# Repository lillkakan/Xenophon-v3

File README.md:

# Xenophon v3 split keyboard

Xenophon is a split keyboard with a design based on the ErgoDox EZ but for less keys for the thumps and another layout for the side keys.

## Features

### Ortholinear design

The keyboard features an ortholinear design based on the ErgoDox EZ.

### 70 buttons

The keyboard features 70 buttons to replicate a standard 60% keyboard as much as possible.
The Default layout is in swedish and has all the letters and numbers.

### TRS jack connection

The PCB is designed with a trs jack nicley placed between the tilted keys.
The two processors sent data through the serial bitbang protocol.

### Smart flashing design

With Usb on both sides it's easy to flash both processors.

### USB-C

The PCB features two usb type c ports with capability to connect via a usb-c to usb-c cable or a standard usb-c to usb-a cable.

### 3D printable chassi

The chassi for the keyboard is 3D printable and is designed to be as small as possible while still protecting the PCB and the electrical components.

## Made with

Quantum Mechanical Keyboard Firmware: [qmk_firmware](https://github.com/qmk/qmk_firmware)

### Made with help from

Keyboard layout editor: [keyboard-layout-editor.com](http://www.keyboard-layout-editor.com/)

Parametric Mechanical Keycap Library: [KeyV2](https://github.com/rsheldiii/KeyV2)

Keyboard Firmware Builder: [kbfirmware.com](https://kbfirmware.com/)

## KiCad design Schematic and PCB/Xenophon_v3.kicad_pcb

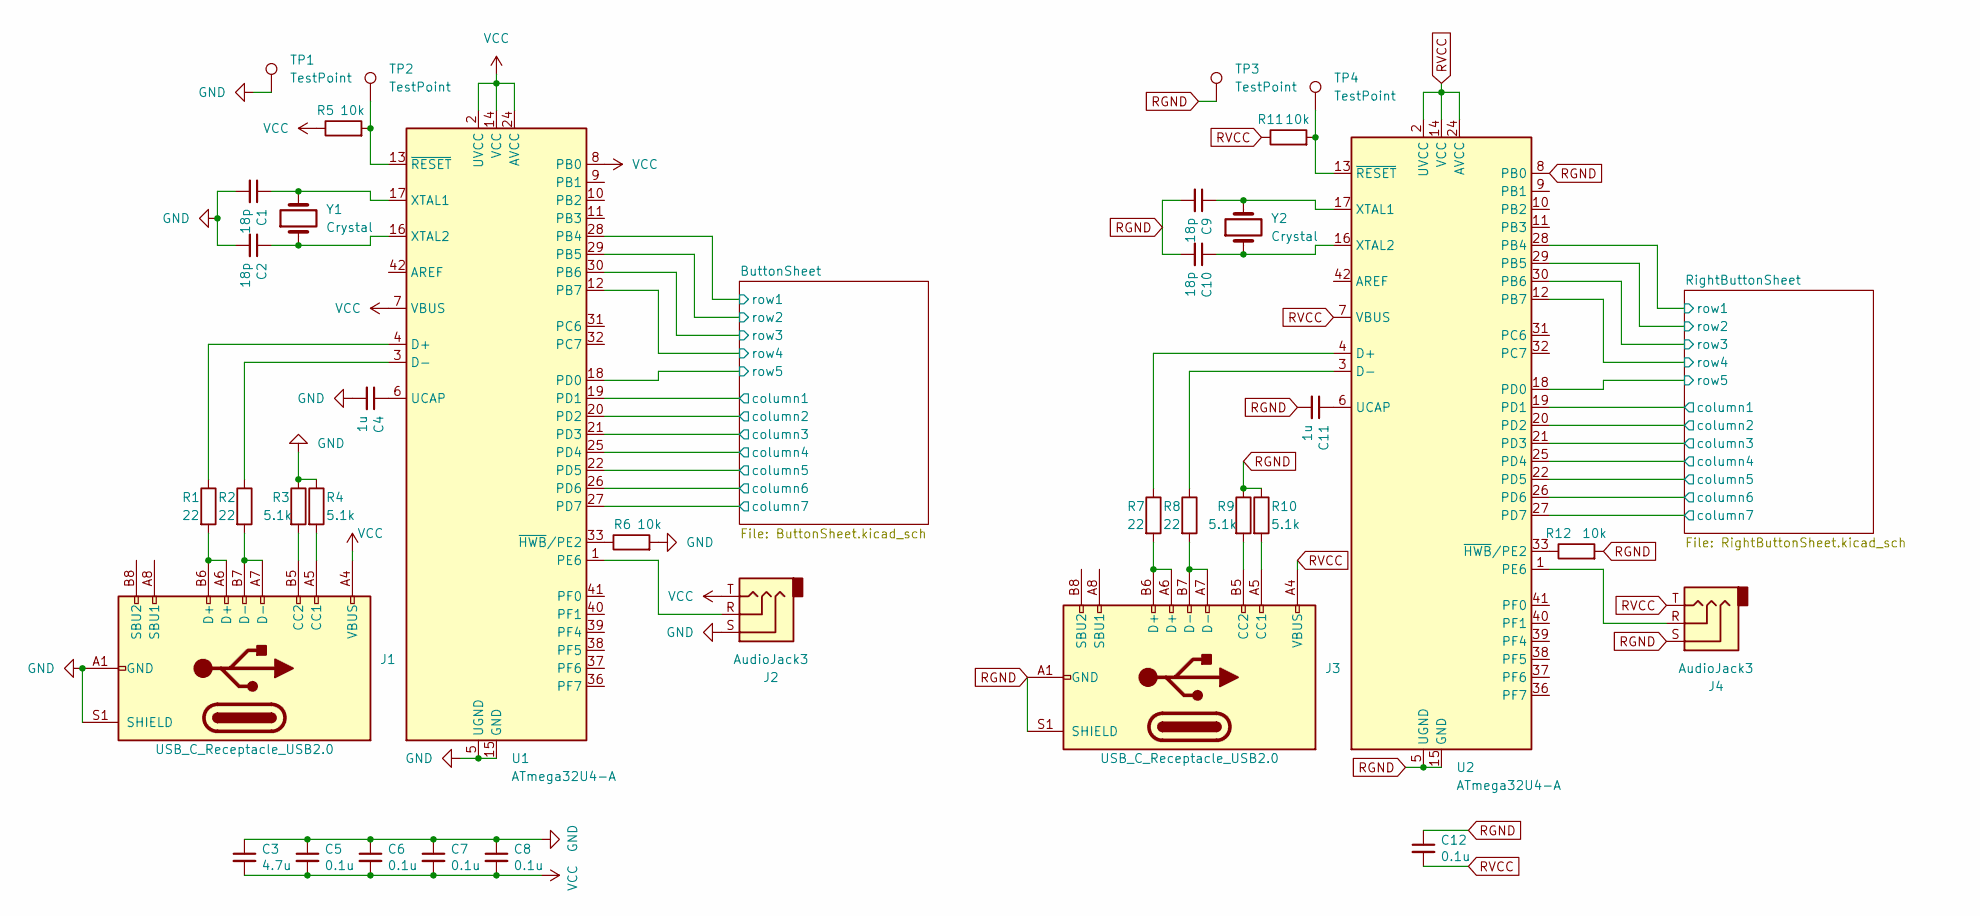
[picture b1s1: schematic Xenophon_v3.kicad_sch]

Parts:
C1, C2, C9, C10: 18p; C_1206_3216Metric
C3: 4.7u; C_1206_3216Metric
C4, C11: 1u; C_1206_3216Metric
C5, C6, C7, C8, C12: 0.1u; C_1206_3216Metric
J1, J3: USB_C_Receptacle_USB2.0; USB_C_Receptacle_HRO_TYPE-C-31-M-12
J2, J4: AudioJack3; Jack_3.5mm_Switronic_ST-005-G_horizontal
R1, R2, R7, R8: 22; R_1206_3216Metric
R3, R4, R9, R10: 5.1k; R_1206_3216Metric
R5, R6, R11, R12: 10k; R_1206_3216Metric
TP1, TP2, TP3, TP4: TestPoint; TestPoint_THTPad_2.0x2.0mm_Drill1.0mm
U1, U2: ATmega32U4-A; TQFP-44_10x10mm_P0.8mm
Y1, Y2: Crystal; Crystal_SMD_2016-4Pin_2.0x1.6mm

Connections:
/ButtonSheet/column1: U1.19 (PD1); also elsewhere on the board
/ButtonSheet/column2: U1.20 (PD2); also elsewhere on the board
/ButtonSheet/column3: U1.21 (PD3); also elsewhere on the board
/ButtonSheet/column4: U1.25 (PD4); also elsewhere on the board
/ButtonSheet/column5: U1.22 (PD5); also elsewhere on the board
/ButtonSheet/column6: U1.26 (PD6); also elsewhere on the board
/ButtonSheet/column7: U1.27 (PD7); also elsewhere on the board
/ButtonSheet/row1: U1.28 (PB4); also elsewhere on the board
/ButtonSheet/row2: U1.29 (PB5); also elsewhere on the board
/ButtonSheet/row3: U1.30 (PB6); also elsewhere on the board
/ButtonSheet/row4: U1.12 (PB7); also elsewhere on the board
/ButtonSheet/row5: U1.18 (PD0); also elsewhere on the board
/RightButtonSheet/column1: U2.19 (PD1); also elsewhere on the board
/RightButtonSheet/column2: U2.20 (PD2); also elsewhere on the board
/RightButtonSheet/column3: U2.21 (PD3); also elsewhere on the board
/RightButtonSheet/column4: U2.25 (PD4); also elsewhere on the board
/RightButtonSheet/column5: U2.22 (PD5); also elsewhere on the board
/RightButtonSheet/column6: U2.26 (PD6); also elsewhere on the board
/RightButtonSheet/column7: U2.27 (PD7); also elsewhere on the board
/RightButtonSheet/row1: U2.28 (PB4); also elsewhere on the board
/RightButtonSheet/row2: U2.29 (PB5); also elsewhere on the board
/RightButtonSheet/row3: U2.30 (PB6); also elsewhere on the board
/RightButtonSheet/row4: U2.12 (PB7); also elsewhere on the board
/RightButtonSheet/row5: U2.18 (PD0); also elsewhere on the board
GND: C1.2, C2.2, C3.1, C4.2, C5.1, C6.1, C7.1, C8.1, J1.A1 (GND), J1.A12 (GND), J1.B1 (GND), J1.B12 (GND), J1.S1 (SHIELD), J2.S, R3.1, R4.1, R6.2, TP1.1, U1.5 (UGND), U1.15 (GND), U1.23 (GND), U1.35 (GND), U1.43 (GND), Y1.3, Y1.4
unnamed: C1.1, U1.17 (XTAL1), Y1.2
unnamed: C2.1, U1.16 (XTAL2), Y1.1
unnamed: C4.1, U1.6 (UCAP)
unnamed: C9.1, U2.17 (XTAL1), Y2.2
unnamed: C10.1, U2.16 (XTAL2), Y2.1
unnamed: C11.1, U2.6 (UCAP)
unnamed: J1.A5 (CC1), R4.2
unnamed: J1.A6 (D+), J1.B6 (D+), R1.2
unnamed: J1.A7 (D-), J1.B7 (D-), R2.2
unnamed: J1.B5 (CC2), R3.2
unnamed: J2.R, U1.1 (PE6)
unnamed: J3.A5 (CC1), R10.2
unnamed: J3.B5 (CC2), R9.2
unnamed: J3.A6 (D+), J3.B6 (D+), R7.2
unnamed: J3.A7 (D-), J3.B7 (D-), R8.2
unnamed: J4.R, U2.1 (PE6)
unnamed: R1.1, U1.4 (D+)
unnamed: R2.1, U1.3 (D-)
unnamed: R5.2, TP2.1, U1.13 (~RESET)
unnamed: R6.1, U1.33 (~HWB/PE2)
unnamed: R7.1, U2.4 (D+)
unnamed: R8.1, U2.3 (D-)
unnamed: R11.2, TP4.1, U2.13 (~RESET)
unnamed: R12.1, U2.33 (~HWB/PE2)
RGND: C9.2, C10.2, C11.2, C12.1, J3.A1 (GND), J3.A12 (GND), J3.B1 (GND), J3.B12 (GND), J3.S1 (SHIELD), J4.S, R9.1, R10.1, R12.2, TP3.1, U2.5 (UGND), U2.8 (PB0), U2.15 (GND), U2.23 (GND), U2.35 (GND), U2.43 (GND), Y2.3, Y2.4
RVCC: C12.2, J3.A4 (VBUS), J3.A9 (VBUS), J3.B4 (VBUS), J3.B9 (VBUS), J4.T, R11.1, U2.2 (UVCC), U2.7 (VBUS), U2.14 (VCC), U2.24 (AVCC), U2.34 (VCC), U2.44 (AVCC)
VCC: C3.2, C5.2, C6.2, C7.2, C8.2, J1.A4 (VBUS), J1.A9 (VBUS), J1.B4 (VBUS), J1.B9 (VBUS), J2.T, R5.1, U1.2 (UVCC), U1.7 (VBUS), U1.8 (PB0), U1.14 (VCC), U1.24 (AVCC), U1.34 (VCC), U1.44 (AVCC)

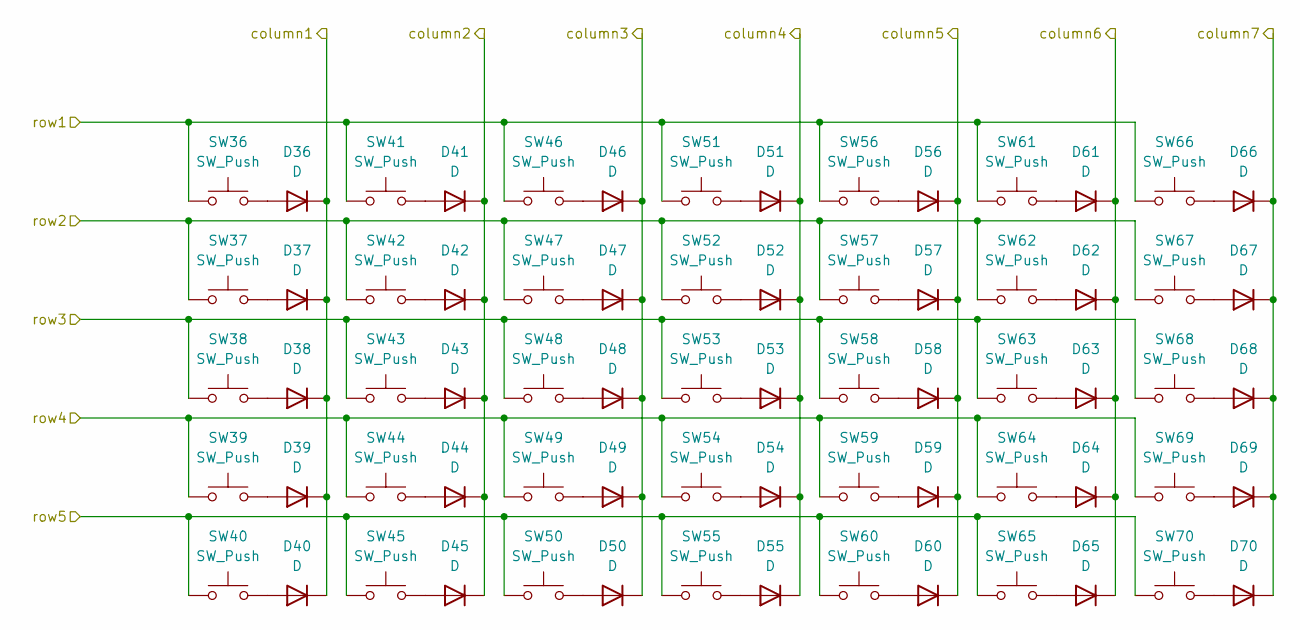
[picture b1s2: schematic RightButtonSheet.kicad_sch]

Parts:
D36, D37, D38, D39, D40, D41, D42, D43, D44, D45, D46, D47, D48, D49, D50, D51, D52, D53, D54, D55, D56, D57, D58, D59, D60, D61, D62, D63, D64, D65, D66, D67, D68, D69, D70: D; D_1206_3216Metric
SW36, SW37, SW38, SW39, SW40, SW41, SW42, SW43, SW44, SW45, SW46, SW47, SW48, SW49, SW50, SW51, SW52, SW53, SW54, SW55, SW56, SW57, SW58, SW59, SW60, SW61, SW62, SW63, SW64, SW65: SW_Push; SW_Cherry_MX_1.00u_PCB
SW66, SW67, SW68, SW69, SW70: SW_Push; SW_Cherry_MX_1.50u_PCB

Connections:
/RightButtonSheet/column1: D36.1 (K), D37.1 (K), D38.1 (K), D39.1 (K), D40.1 (K); also elsewhere on the board
/RightButtonSheet/column2: D41.1 (K), D42.1 (K), D43.1 (K), D44.1 (K), D45.1 (K); also elsewhere on the board
/RightButtonSheet/column3: D46.1 (K), D47.1 (K), D48.1 (K), D49.1 (K), D50.1 (K); also elsewhere on the board
/RightButtonSheet/column4: D51.1 (K), D52.1 (K), D53.1 (K), D54.1 (K), D55.1 (K); also elsewhere on the board
/RightButtonSheet/column5: D56.1 (K), D57.1 (K), D58.1 (K), D59.1 (K), D60.1 (K); also elsewhere on the board
/RightButtonSheet/column6: D61.1 (K), D62.1 (K), D63.1 (K), D64.1 (K), D65.1 (K); also elsewhere on the board
/RightButtonSheet/column7: D66.1 (K), D67.1 (K), D68.1 (K), D69.1 (K), D70.1 (K); also elsewhere on the board
/RightButtonSheet/row1: SW36.1, SW41.1, SW46.1, SW51.1, SW56.1, SW61.1, SW66.1; also elsewhere on the board
/RightButtonSheet/row2: SW37.1, SW42.1, SW47.1, SW52.1, SW57.1, SW62.1, SW67.1; also elsewhere on the board
/RightButtonSheet/row3: SW38.1, SW43.1, SW48.1, SW53.1, SW58.1, SW63.1, SW68.1; also elsewhere on the board
/RightButtonSheet/row4: SW39.1, SW44.1, SW49.1, SW54.1, SW59.1, SW64.1, SW69.1; also elsewhere on the board
/RightButtonSheet/row5: SW40.1, SW45.1, SW50.1, SW55.1, SW60.1, SW65.1, SW70.1; also elsewhere on the board
unnamed: D36.2 (A), SW36.2
unnamed: D37.2 (A), SW37.2
unnamed: D38.2 (A), SW38.2
unnamed: D39.2 (A), SW39.2
unnamed: D40.2 (A), SW40.2
unnamed: D41.2 (A), SW41.2
unnamed: D42.2 (A), SW42.2
unnamed: D43.2 (A), SW43.2
unnamed: D44.2 (A), SW44.2
unnamed: D45.2 (A), SW45.2
unnamed: D46.2 (A), SW46.2
unnamed: D47.2 (A), SW47.2
unnamed: D48.2 (A), SW48.2
unnamed: D49.2 (A), SW49.2
unnamed: D50.2 (A), SW50.2
unnamed: D51.2 (A), SW51.2
unnamed: D52.2 (A), SW52.2
unnamed: D53.2 (A), SW53.2
unnamed: D54.2 (A), SW54.2
unnamed: D55.2 (A), SW55.2
unnamed: D56.2 (A), SW56.2
unnamed: D57.2 (A), SW57.2
unnamed: D58.2 (A), SW58.2
unnamed: D59.2 (A), SW59.2
unnamed: D60.2 (A), SW60.2
unnamed: D61.2 (A), SW61.2
unnamed: D62.2 (A), SW62.2
unnamed: D63.2 (A), SW63.2
unnamed: D64.2 (A), SW64.2
unnamed: D65.2 (A), SW65.2
unnamed: D66.2 (A), SW66.2
unnamed: D67.2 (A), SW67.2
unnamed: D68.2 (A), SW68.2
unnamed: D69.2 (A), SW69.2
unnamed: D70.2 (A), SW70.2

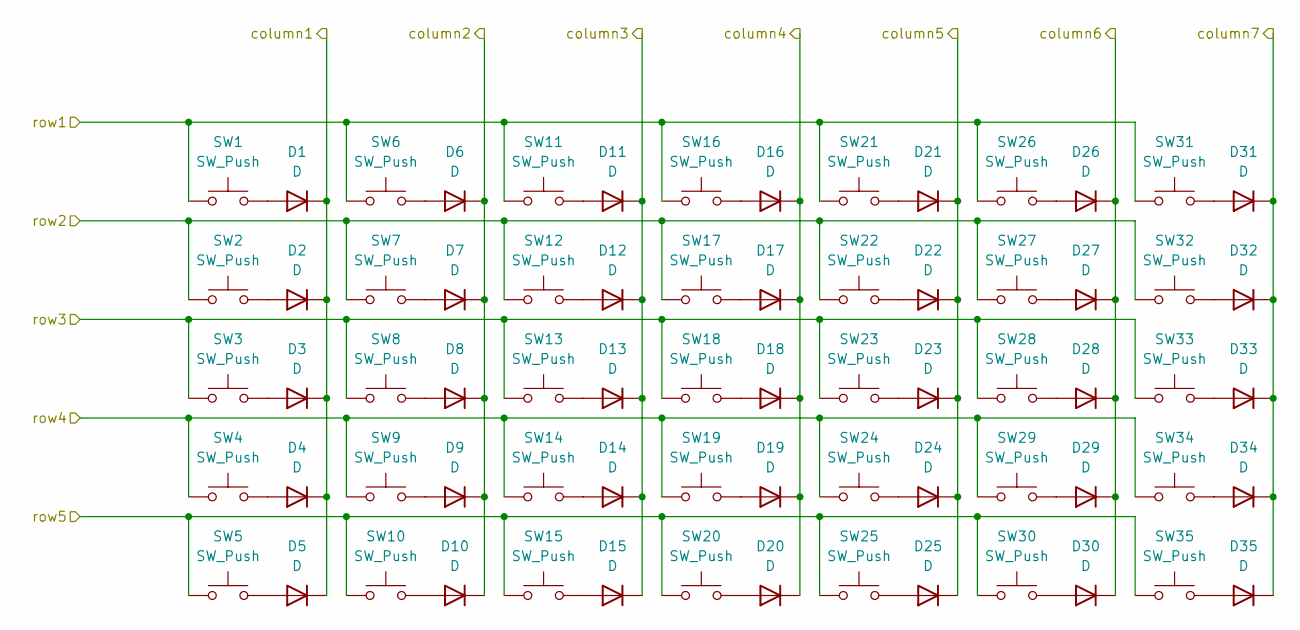
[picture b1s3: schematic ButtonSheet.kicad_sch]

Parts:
D1, D2, D3, D4, D5, D6, D7, D8, D9, D10, D11, D12, D13, D14, D15, D16, D17, D18, D19, D20, D21, D22, D23, D24, D25, D26, D27, D28, D29, D30, D31, D32, D33, D34, D35: D; D_1206_3216Metric
SW1, SW2, SW3, SW4, SW5: SW_Push; SW_Cherry_MX_1.50u_PCB
SW6, SW7, SW8, SW9, SW10, SW11, SW12, SW13, SW14, SW15, SW16, SW17, SW18, SW19, SW20, SW21, SW22, SW23, SW24, SW25, SW26, SW27, SW28, SW29, SW30, SW31, SW32, SW33, SW34, SW35: SW_Push; SW_Cherry_MX_1.00u_PCB

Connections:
/ButtonSheet/column1: D1.1 (K), D2.1 (K), D3.1 (K), D4.1 (K), D5.1 (K); also elsewhere on the board
/ButtonSheet/column2: D6.1 (K), D7.1 (K), D8.1 (K), D9.1 (K), D10.1 (K); also elsewhere on the board
/ButtonSheet/column3: D11.1 (K), D12.1 (K), D13.1 (K), D14.1 (K), D15.1 (K); also elsewhere on the board
/ButtonSheet/column4: D16.1 (K), D17.1 (K), D18.1 (K), D19.1 (K), D20.1 (K); also elsewhere on the board
/ButtonSheet/column5: D21.1 (K), D22.1 (K), D23.1 (K), D24.1 (K), D25.1 (K); also elsewhere on the board
/ButtonSheet/column6: D26.1 (K), D27.1 (K), D28.1 (K), D29.1 (K), D30.1 (K); also elsewhere on the board
/ButtonSheet/column7: D31.1 (K), D32.1 (K), D33.1 (K), D34.1 (K), D35.1 (K); also elsewhere on the board
/ButtonSheet/row1: SW1.1, SW6.1, SW11.1, SW16.1, SW21.1, SW26.1, SW31.1; also elsewhere on the board
/ButtonSheet/row2: SW2.1, SW7.1, SW12.1, SW17.1, SW22.1, SW27.1, SW32.1; also elsewhere on the board
/ButtonSheet/row3: SW3.1, SW8.1, SW13.1, SW18.1, SW23.1, SW28.1, SW33.1; also elsewhere on the board
/ButtonSheet/row4: SW4.1, SW9.1, SW14.1, SW19.1, SW24.1, SW29.1, SW34.1; also elsewhere on the board
/ButtonSheet/row5: SW5.1, SW10.1, SW15.1, SW20.1, SW25.1, SW30.1, SW35.1; also elsewhere on the board
unnamed: D1.2 (A), SW1.2
unnamed: D2.2 (A), SW2.2
unnamed: D3.2 (A), SW3.2
unnamed: D4.2 (A), SW4.2
unnamed: D5.2 (A), SW5.2
unnamed: D6.2 (A), SW6.2
unnamed: D7.2 (A), SW7.2
unnamed: D8.2 (A), SW8.2
unnamed: D9.2 (A), SW9.2
unnamed: D10.2 (A), SW10.2
unnamed: D11.2 (A), SW11.2
unnamed: D12.2 (A), SW12.2
unnamed: D13.2 (A), SW13.2
unnamed: D14.2 (A), SW14.2
unnamed: D15.2 (A), SW15.2
unnamed: D16.2 (A), SW16.2
unnamed: D17.2 (A), SW17.2
unnamed: D18.2 (A), SW18.2
unnamed: D19.2 (A), SW19.2
unnamed: D20.2 (A), SW20.2
unnamed: D21.2 (A), SW21.2
unnamed: D22.2 (A), SW22.2
unnamed: D23.2 (A), SW23.2
unnamed: D24.2 (A), SW24.2
unnamed: D25.2 (A), SW25.2
unnamed: D26.2 (A), SW26.2
unnamed: D27.2 (A), SW27.2
unnamed: D28.2 (A), SW28.2
unnamed: D29.2 (A), SW29.2
unnamed: D30.2 (A), SW30.2
unnamed: D31.2 (A), SW31.2
unnamed: D32.2 (A), SW32.2
unnamed: D33.2 (A), SW33.2
unnamed: D34.2 (A), SW34.2
unnamed: D35.2 (A), SW35.2

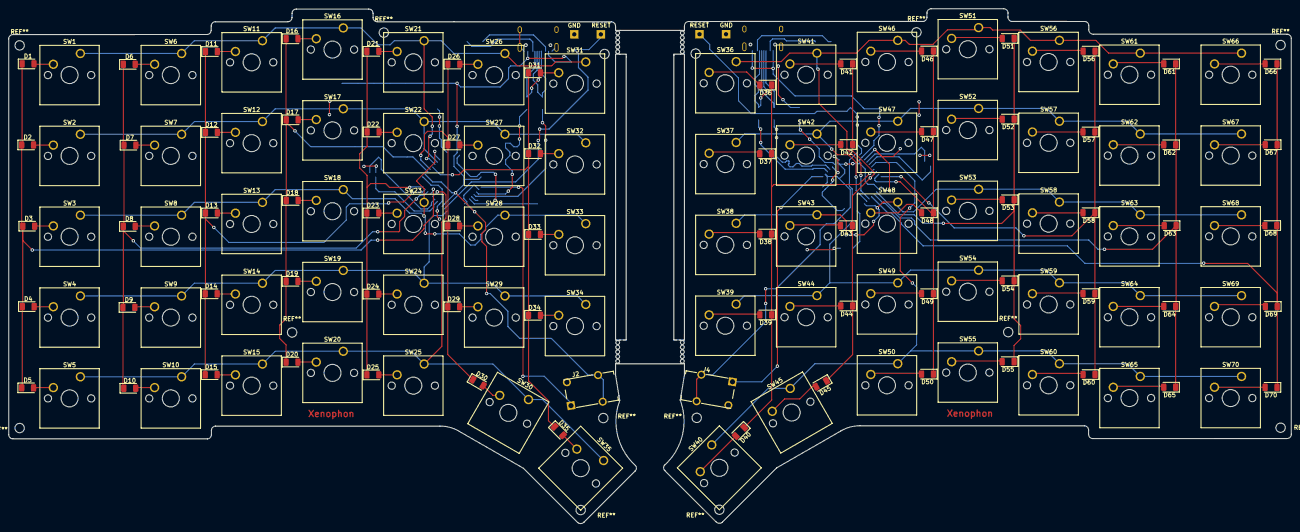
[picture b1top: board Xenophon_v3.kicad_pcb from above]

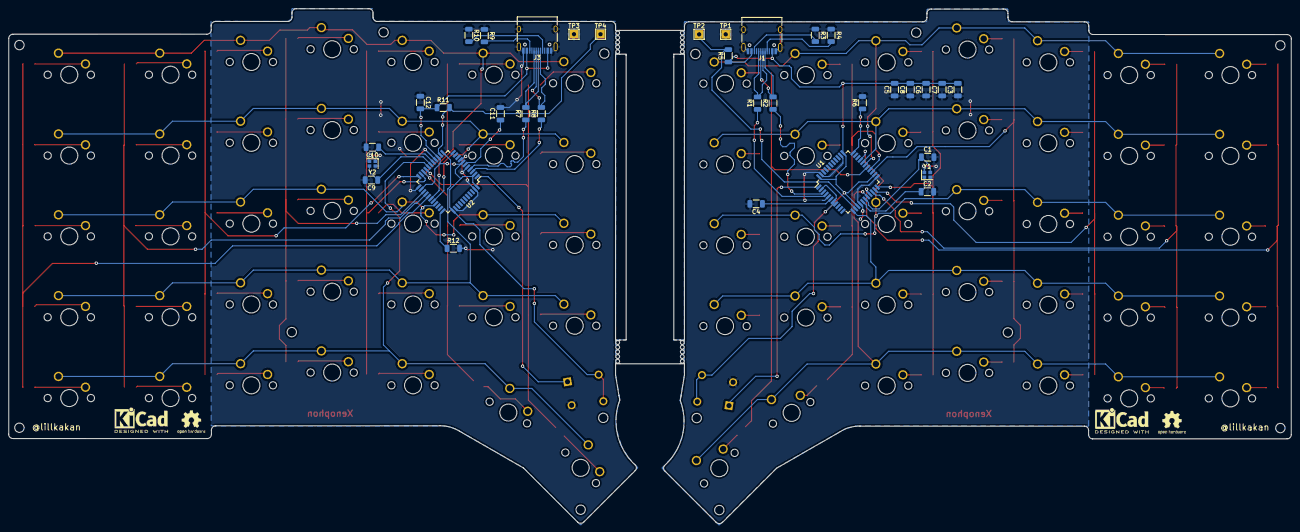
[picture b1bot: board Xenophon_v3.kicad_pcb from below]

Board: 2 copper layers, 301.5 x 121.0 mm, 176 parts (34 on the bottom side), 122 nets.

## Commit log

2022-08-21 First design
2022-08-21 Small rerouting fixes
2022-08-21 Panelized the pcb
2023-08-28 Updated readme and qmk code
2023-08-28 Updated gerber
